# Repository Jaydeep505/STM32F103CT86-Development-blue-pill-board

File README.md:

# STM32F103CT86-Development-blue-pill-board
Schematic and Pcb of STM32F103CT86 Development (blue pill)board

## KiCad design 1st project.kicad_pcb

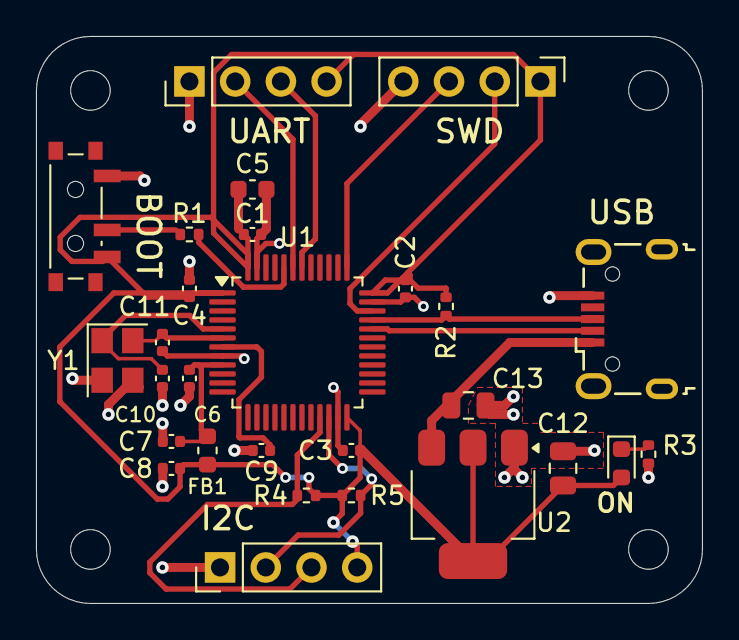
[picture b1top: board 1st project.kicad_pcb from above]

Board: 2 copper layers, 37.0 x 31.5 mm, 32 parts (0 on the bottom side), 18 nets.

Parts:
C1, C2, C3, C4, C9: 100n; C_0402_1005Metric
C5: 10u; C_0603_1608Metric
C6: 10n; C_0402_1005Metric
C7, C8: 1u; C_0402_1005Metric
C10, C11: 10p; C_0402_1005Metric
C12, C13: 22u; C_0805_2012Metric
D1: RED; LED_0603_1608Metric
FB1: 120R; L_0603_1608Metric
H1, H2, H3, H4: MountingHole; MountingHole_2.2mm_M2
J1: USB_B_Mini; USB_Micro-B_Wuerth_629105150521
J2, J3, J4: Conn_01x04_Pin; PinHeader_1x04_P2.54mm_Vertical
R1: 10K; R_0402_1005Metric
R2, R3, R4, R5: 1k5; R_0402_1005Metric
SW1: SW_SPDT; SW_SPDT_PCM12
U1: STM32F103C8T6; LQFP-48_7x7mm_P0.5mm
U2: AMS1117-3.3; SOT-223-3_TabPin2
Y1: 16MHZ; Crystal_SMD_3225-4Pin_3.2x2.5mm

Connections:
+3.3V: C1.1, C2.1, C3.1, C4.1, C5.1, C8.1, C12.2, D1.2 (A), FB1.2, J2.1, J3.4, J4.4, R2.1, R4.1, R5.1, SW1.3 (C), U1.1 (VBAT), U1.24 (VDD), U1.36 (VDD), U1.48 (VDD), U2.2 (VO)
+3.3VA: C6.1, C7.1, FB1.1, U1.9 (VDDA)
/BOOT0: R1.2, U1.44 (BOOT0)
/HSC_IN: C10.1, U1.5 (PD0), Y1.1
/HSC_OUT: C11.1, U1.6 (PD1), Y1.4
/I2C2_SCL: J4.3, R4.2, U1.21 (PB10)
/I2C2_SDA: J4.2, R5.2, U1.22 (PB11)
/NRST: C9.1, U1.7 (NRST)
/PWR_LED_K: D1.1 (K), R3.1
/SWDCLK: J2.3, U1.37 (PA14)
/SWDIO: J2.2, U1.34 (PA13)
/SW_BOOT0: R1.1, SW1.2 (B)
/USART1_RX: J3.2, U1.43 (PB7)
/USART1_TX: J3.3, U1.42 (PB6)
/USB_D+: J1.3 (D+), R2.2, U1.33 (PA12)
/USB_D-: J1.2 (D-), U1.32 (PA11)
GND: C1.2, C2.2, C3.2, C4.2, C5.2, C6.2, C7.2, C8.2, C9.2, C10.2, C11.2, C12.1, C13.1, J1.5 (GND), J2.4, J3.1, J4.1, R3.2, SW1.1 (A), U1.8 (VSSA), U1.23 (VSS), U1.35 (VSS), U1.47 (VSS), U2.1 (GND), Y1.2, Y1.3
VBUS: C13.2, J1.1 (VBUS), U2.3 (VI)
